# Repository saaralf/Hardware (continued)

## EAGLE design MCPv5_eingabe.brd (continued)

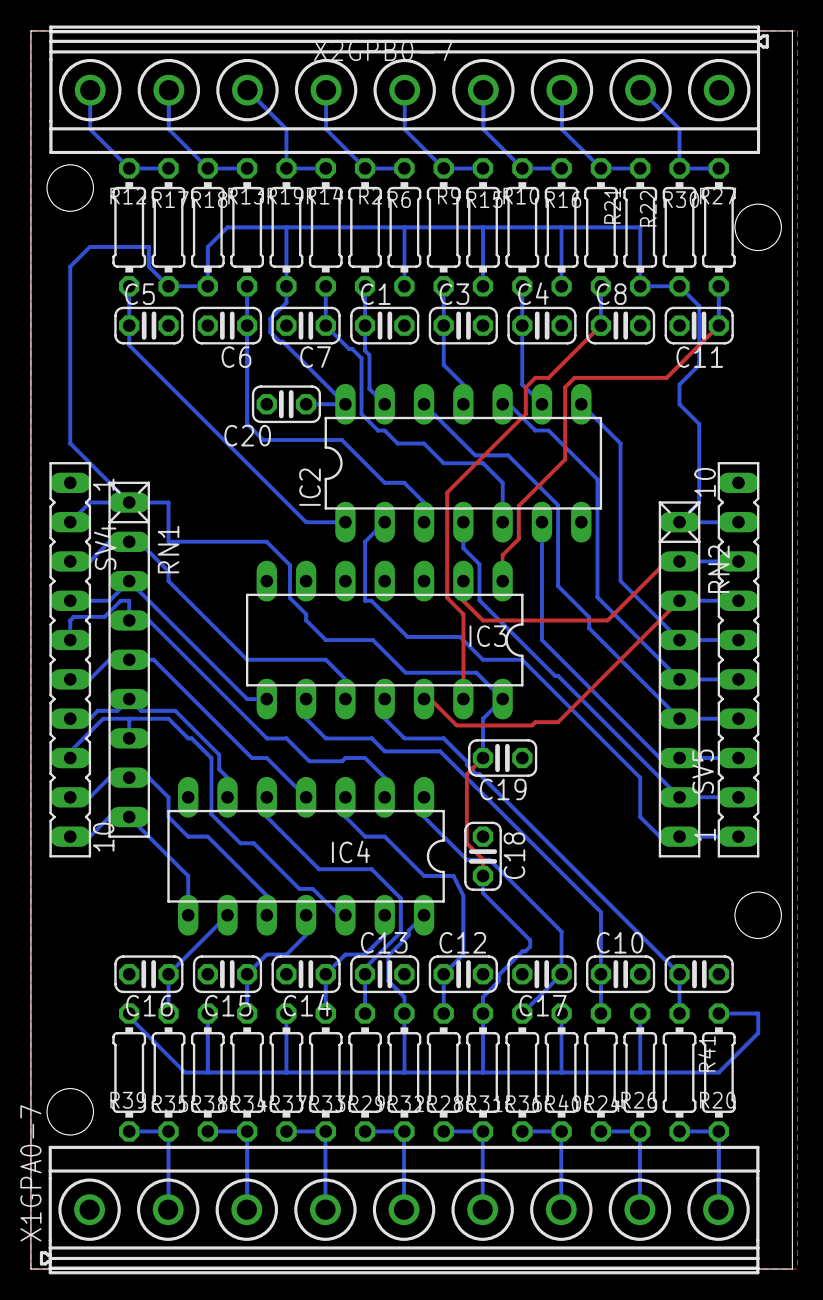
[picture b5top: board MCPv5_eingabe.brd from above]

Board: 2 copper layers, 49.2 x 80.0 mm, 60 parts (0 on the bottom side), 50 nets.

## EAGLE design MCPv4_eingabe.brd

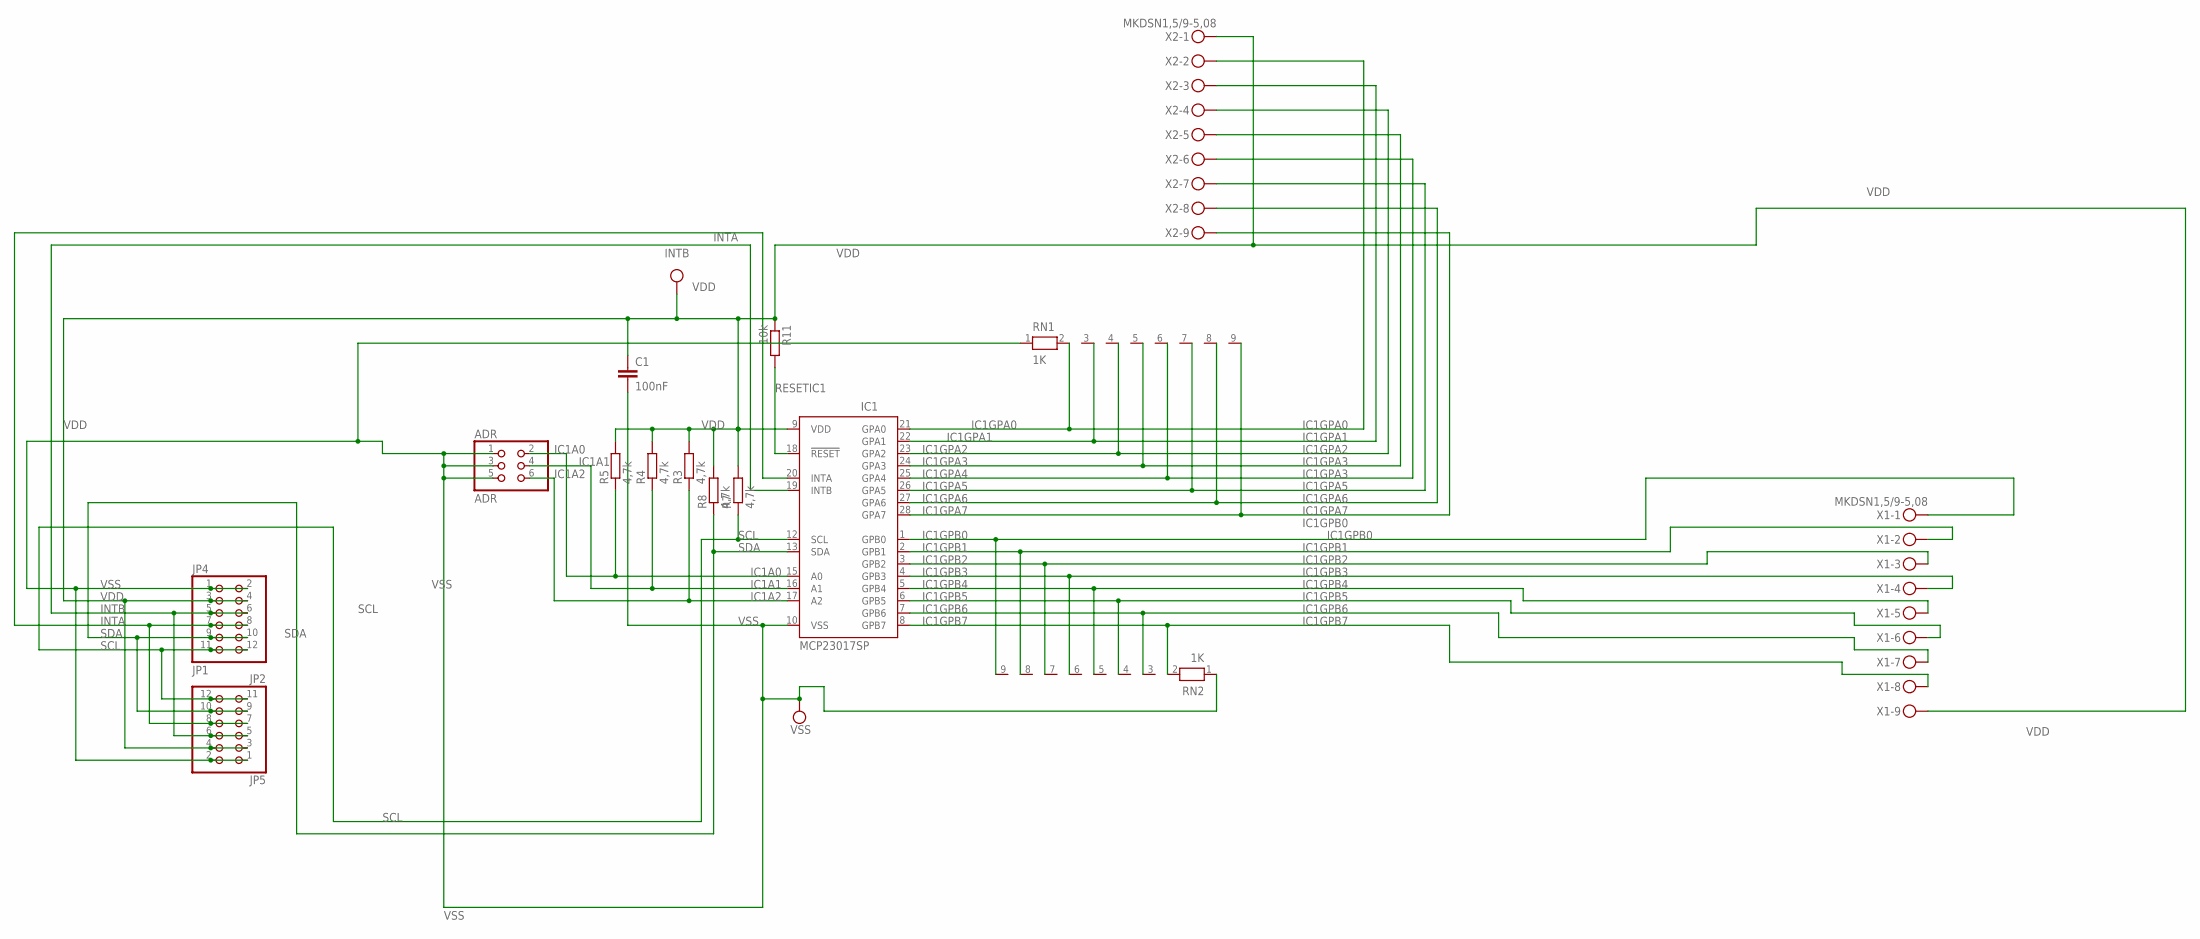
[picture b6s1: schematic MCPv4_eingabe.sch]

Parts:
ADR: ADR; 2X03
C1: 100nF; C025_050-025X075
IC1: MCP23017SP; DIL28-3
JP4: JP1; 2X06/90
JP5: JP2; 2X06/90
R3, R4, R5, R7, R8: 4,7k; 0204/7
R11: 10k; 0204/7
RN1, RN2: 1K; RN-9
X1, X2: MKDSN1,5/9-5,08

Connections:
IC1A0: ADR.2, IC1.15 (A0), R5.1
IC1A1: ADR.4, IC1.16 (A1), R4.1
IC1A2: ADR.6, IC1.17 (A2), R3.1
IC1GPA0: IC1.21 (GPA0), RN1.2, X2.2
IC1GPA1: IC1.22 (GPA1), RN1.3, X2.3
IC1GPA2: IC1.23 (GPA2), RN1.4, X2.4
IC1GPA3: IC1.24 (GPA3), RN1.5, X2.5
IC1GPA4: IC1.25 (GPA4), RN1.6, X2.6
IC1GPA5: IC1.26 (GPA5), RN1.7, X2.7
IC1GPA6: IC1.27 (GPA6), RN1.8, X2.8
IC1GPA7: IC1.28 (GPA7), RN1.9, X2.9
IC1GPB0: IC1.1 (GPB0), RN2.9, X1.1
IC1GPB1: IC1.2 (GPB1), RN2.8, X1.2
IC1GPB2: IC1.3 (GPB2), RN2.7, X1.3
IC1GPB3: IC1.4 (GPB3), RN2.6, X1.4
IC1GPB4: IC1.5 (GPB4), RN2.5, X1.5
IC1GPB5: IC1.6 (GPB5), RN2.4, X1.6
IC1GPB6: IC1.7 (GPB6), RN2.3, X1.7
IC1GPB7: IC1.8 (GPB7), RN2.2, X1.8
INTA: IC1.20 (INTA), JP4.7, JP4.8, JP5.7, JP5.8
INTB: IC1.19 (INTB), JP4.5, JP4.6, JP5.5, JP5.6
RESETIC1: IC1.18 (!RESET), R11.2
SCL: IC1.12 (SCL), JP4.11, JP4.12, JP5.11, JP5.12, R7.1
SDA: IC1.13 (SDA), JP4.9, JP4.10, JP5.9, JP5.10, R8.1
VDD: C1.1, IC1.9 (VDD), JP4.3, JP4.4, JP5.3, JP5.4, R3.2, R4.2, R5.2, R7.2, R8.2, R11.1, X1.9, X2.1
VSS: ADR.1, ADR.3, ADR.5, C1.2, IC1.10 (VSS), JP4.1, JP4.2, JP5.1, JP5.2, RN1.1, RN2.1

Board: 2 copper layers, 16 parts (0 on the bottom side), 26 nets, no tracks yet.

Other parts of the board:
DRILEGEND: DRILEGEND

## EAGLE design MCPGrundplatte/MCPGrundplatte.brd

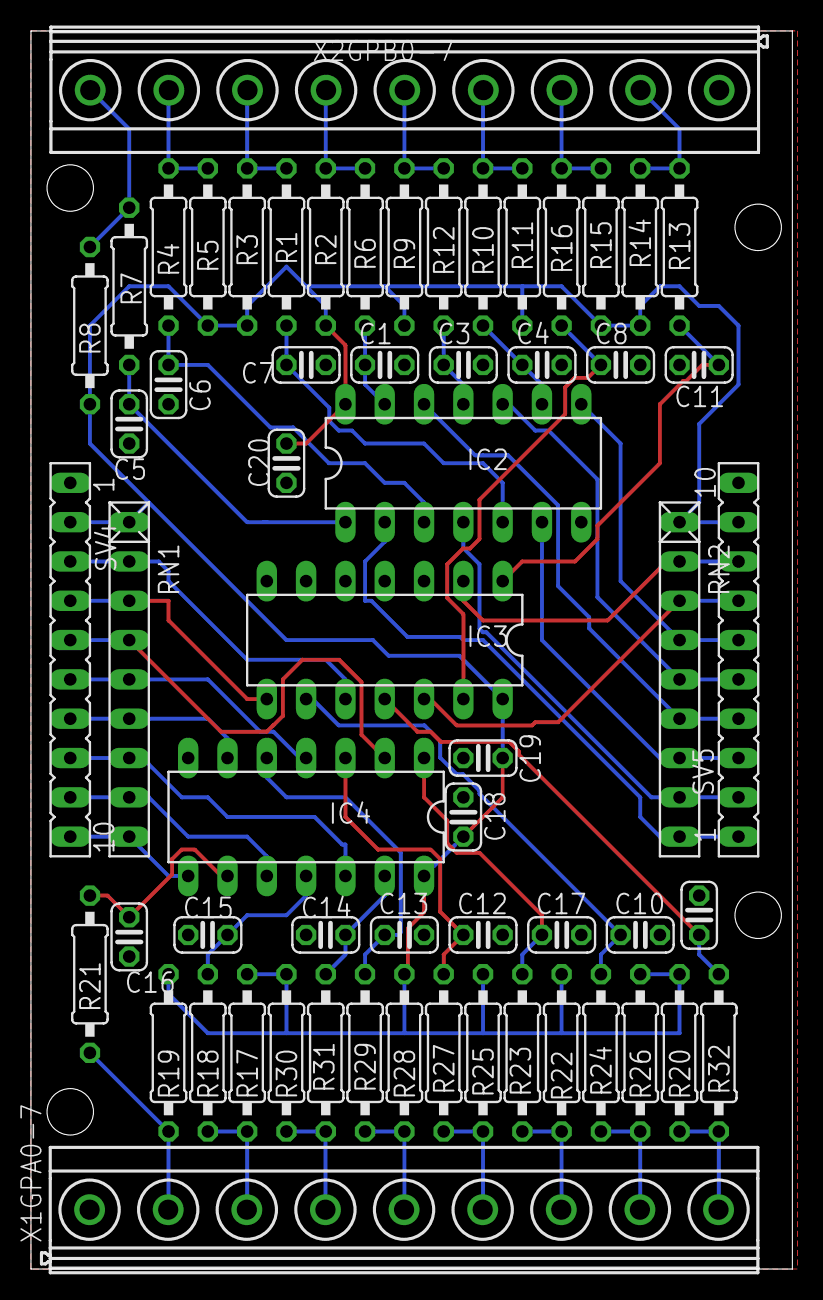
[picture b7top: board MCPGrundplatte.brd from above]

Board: 2 copper layers, 49.2 x 80.0 mm, 60 parts (0 on the bottom side), 50 nets.

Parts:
C1: 100Nf; C025-024X044
C3, C4, C5, C6, C7, C8, C10, C11, C12, C13, C14, C15, C16, C17, C18, C19, C20, C21: 100nF; C025-024X044
IC2, IC3, IC4: 74HC14N; DIL14
R1, R2, R3, R4, R5, R6, R7, R8, R9, R10, R11, R12, R13, R14, R15, R16, R17, R18, R19, R20, R21, R22, R23, R24, R25, R26, R27, R28, R29, R30, R31, R32: 10k; 0207/10
RN1, RN2: 100K; RN-9
SV4, SV5: FE10
X1GPA0-7, X2GPB0-7: MKDSN1,5/9-5,08

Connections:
GND: C1.2, C3.2, C4.2, C5.2, C6.2, C7.2, C8.2, C10.2, C11.2, C12.2, C13.2, C14.2, C15.2, C16.2, C17.2, C18.1, C19.1, C20.2, C21.2, IC2.7, IC3.3, IC3.4, IC3.5, IC3.6, IC3.7, IC4.7, SV4.1, SV5.10, X1GPA0-7.1, X2GPB0-7.1
GPA0: R20.2, R32.1, X1GPA0-7.9
GPA0.: IC3.10, RN1.2, SV4.3
GPA1: R24.1, R26.2, X1GPA0-7.8
GPA1.: IC3.8, RN1.3, SV4.4
GPA2: R22.2, R23.1, X1GPA0-7.7
GPA2.: IC4.2, RN1.4, SV4.5
GPA3: R25.2, R27.1, X1GPA0-7.6
GPA3.: IC4.4, RN1.5, SV4.6
GPA4: R28.2, R29.1, X1GPA0-7.5
GPA4.: IC4.6, RN1.6, SV4.7
GPA5: R30.2, R31.1, X1GPA0-7.4
GPA5.: IC4.12, RN1.7, SV4.8
GPA6: R17.2, R18.1, X1GPA0-7.3
GPA6.: IC4.10, RN1.8, SV4.9
GPA7: R19.2, R21.1, X1GPA0-7.2
GPA7.: IC4.8, RN1.9, SV4.10
GPB0: R7.1, R8.2, X2GPB0-7.9
GPB0.: IC2.2, RN2.9, SV5.1
GPB1: R4.1, R5.1, X2GPB0-7.8
GPB1.: IC2.4, RN2.8, SV5.2
GPB2: R1.1, R3.2, X2GPB0-7.7
GPB2.: IC2.6, RN2.7, SV5.3
GPB3: R2.2, R6.1, X2GPB0-7.6
GPB3.: IC2.12, RN2.6, SV5.4
GPB4: R9.2, R12.1, X2GPB0-7.5
GPB4.: IC2.10, RN2.5, SV5.5
GPB5: R10.1, R11.2, X2GPB0-7.4
GPB5.: IC2.8, RN2.4, SV5.6
GPB6: R15.2, R16.1, X2GPB0-7.3
GPB6.: IC3.12, RN2.3, SV5.7
GPB7: R13.1, R14.2, X2GPB0-7.2
GPB7.: IC3.2, RN2.2, SV5.8
unnamed: C7.1, IC2.5, R1.2
unnamed: C1.1, IC2.13, R6.2
unnamed: C6.1, IC2.3, R4.2
unnamed: C5.1, IC2.1, R7.2
unnamed: C4.1, IC2.9, R10.2
unnamed: C3.1, IC2.11, R12.2
unnamed: C8.1, IC3.13, R16.2
unnamed: C10.1, IC3.9, R24.2
unnamed: C11.1, IC3.1, R13.2
unnamed: C12.1, IC4.3, R27.2
unnamed: C13.1, IC4.5, R29.2
unnamed: C15.1, IC4.11, R18.2
unnamed: C16.1, IC4.9, R21.2
unnamed: C17.1, IC4.1, R23.2
unnamed: C14.1, IC4.13, R31.2
unnamed: C21.1, IC3.11, R32.2
VDD: C18.2, C19.2, C20.1, IC2.14, IC3.14, IC4.14, R2.1, R3.1, R5.2, R8.1, R9.1, R11.1, R14.1, R15.1, R17.1, R19.1, R20.1, R22.1, R25.1, R26.1, R28.1, R30.1, RN1.1, RN2.1, SV4.2, SV5.9

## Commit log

2021-12-11 Schaltpläne hinzugefügt
2021-12-12 Neuen 16 Fach Output und 8In8Out hinzugefügt
2021-12-12 Neu organisiert
2021-12-19 Neue Hardware
2021-12-19 MCPAufsatzVerzweigerV1
2021-12-19 Neuen OutPut 16x hinzugefügt
2021-12-19 Aktuallisiert
2021-12-19 Siebdruck angepasst, C hinzugefügt
2021-12-24 Aufsatz MCPGrundplatte16xOutput.png
2021-12-24 Add files via upload
    MCPGrundplatte.png
2021-12-24 Add files via upload
    Mega2560 SX Shield.png
2021-12-24 Add files via upload
    MCP23017_AufsatzV1.png
2021-12-24 Add files via upload
    Aufsatz MCP23017_Aufsatz_Verzweiger_V2.png
2021-12-24 Update README.md
    Bilder in README.md aufgenommen
